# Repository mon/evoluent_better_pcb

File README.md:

# Evoluent VM4/VMC/VMD better PCB

Let's face it - the sensor that Evoluent ships with the VerticalMouse series of
mice is at best "OK" and recently, dreadful. While my VM4 and the wireless VMC
was "fine, but office-spec", the VMD jitters, jumps, and cannot keep up with
even moderately fast moves across the mousepad.

So, I created this drop-in replacement PCB to upgrade the sensor to a gaming
grade PMW3360DM, using an atmega32u4 and Arduino.

## Supported models
So far this seems to work with
- VMD
- VMC
- VM4 (large and small)

It *may* work with the VM3.

The current design only supports wired models.

## Installation

The PCB has the same shape and pinouts as the stock PCB and is a drop-in replacement.

### Step 1
Remove the bottom off your mouse - this unfortunately requires
taking some of the non-slip feet off. Be as careful as possible to not mangle
the feet when you remove them, or you will significantly affect the smooth feel
of the mouse.

**It is normal for surface smoothness to be poor after you replace the feet.
When I upgraded my VMD, it took 2-3 weeks to return to normal feeling.**

For the **Large** VerticalMouse D, the screws (some of which are Torx security
bits) are located here: 

For the VerticalMouse **C**, the screws are located here:  

For the **Small** VerticalMouse 4, the screws are located here:  

### Step 2
With the bottom of the mouse removed, unplug all cables from the existing PCB.

The USB cable (the one located at the back of the PCB) can take a fair amount of
force to remove. Ensure you grip at the base of the cable to avoid damage.

The ribbon cables must also be gripped at the base when removing/replacing them,
as they are more fragile than normal cables.

## Step 3
Unscrew and remove the existing PCB. The screws are located here:

## Step 4
Repeat the disassembly steps in reverse.

## Step 5 (Optional)
For shipped PCBs: If the default firmware is not to your liking, customise it
using the Arduino toolchain. See the "Firmware" section (you can skip the
bootloader as the PCB ships with one).

For PCBs you make yourself: You need to flash the bootloader and firmware, see
the "Firmware" section.

## Firmware

- Using the ICSP pins on the left of the PCB, flash the atmega with the Arduino
  Leonardo bootloader.
- Install the AdvMouse library from the [PMW3360_Arduino
  repository](https://github.com/SunjunKim/PMW3360_Arduino)
- Install the Encoder library under Tools -> Manage Libraries
- The Arduino IDE might not automatically recognise the required files for the project to build. They are:
  - `SROM_0x04_Arduino.ino`
  - `better_evoluent.ino`
  - `usb_rename.cpp`
  - `usb_rename.h`
- Customise your button layout in the struct `button_t buttons[]`.
  - The pin map is:
  - 10: Top mouse button
  - 6: Middle mouse button
  - 4: Lower mouse button
  - 12: Scrollwheel click (for mice that have one)
  - A0: Lower thumb button
  - 2: Upper thumb button
  - (Thumb button pins are reversed on the VMC)
  - 8: Sensitivity/DPI button
- (Optional) Adjust the DPI increments in `dpi_steps[]`
- (Optional) If your buttons are chattery and double-clicking when they
  shouldn't, increase `DEBOUNCE` from 20 to some higher number, such as 50.
- (Optional) Rename the mouse's device name using the `USBRename` line. The
  default is `Evoluent VMD` with manufacturer `mon.im`.
- flash evoluent_better_pcb.ino, selecting Arduino Leonardo as the device type.

I recommend using Device Manager to assign a very high COM port number to the
mouse - that way, you won't accidentally reflash the mouse when working with
other Arduino projects.

The default firmware is basic, but functional. It is based on PMW3360_Arduino's
PMW3360DM-Mouse example and extended for my own uses. It has a serial interface
to configure mouse parameters which is useful when nailing down your preferred
DPI.

The default DPI is the second entry in the list. Clicking the DPI button when
the DPI indicator LEDs are off will show the current DPI. Clicking again within
5 seconds will move the selected DPI through the list. This does not persist
over a power cycle.

## The PCB

It uses the recommended circuit for the PMW3360, with a 1.8v core voltage and
3.3v IO voltage, with the Arduino also running at 3.3v (not 5v).

The PCB is in the `evoluent` subfolder. There are gerbers in `evoluent/production`.

## Assembly/BOM

There is a full BOM csv in `evoluent/production`.

The PMW3360DM (with lens) can be easily bought from aliexpress for about $10
USD.

The FPC connectors for the buttons can be any thru-hole soldered, 1mm pitch
connector. The schematic has the JST 08FMZ-BT/10FMZ-BT, but I ended up buying
something else.

The USB connector is compatible with JST-PH.

The other components are fairly standard, and if the 3v3/1v8 regulators are
unavailable, there will be pin-compatible replacements easily available.

## Support

I use this PCB in my mouse daily. I have been running it for almost 2 years now
without issues, so please get in contact if you are having problems.

You are free to manufacture this PCB and sell it on Tindie etc, just remember to
provide attribution :)

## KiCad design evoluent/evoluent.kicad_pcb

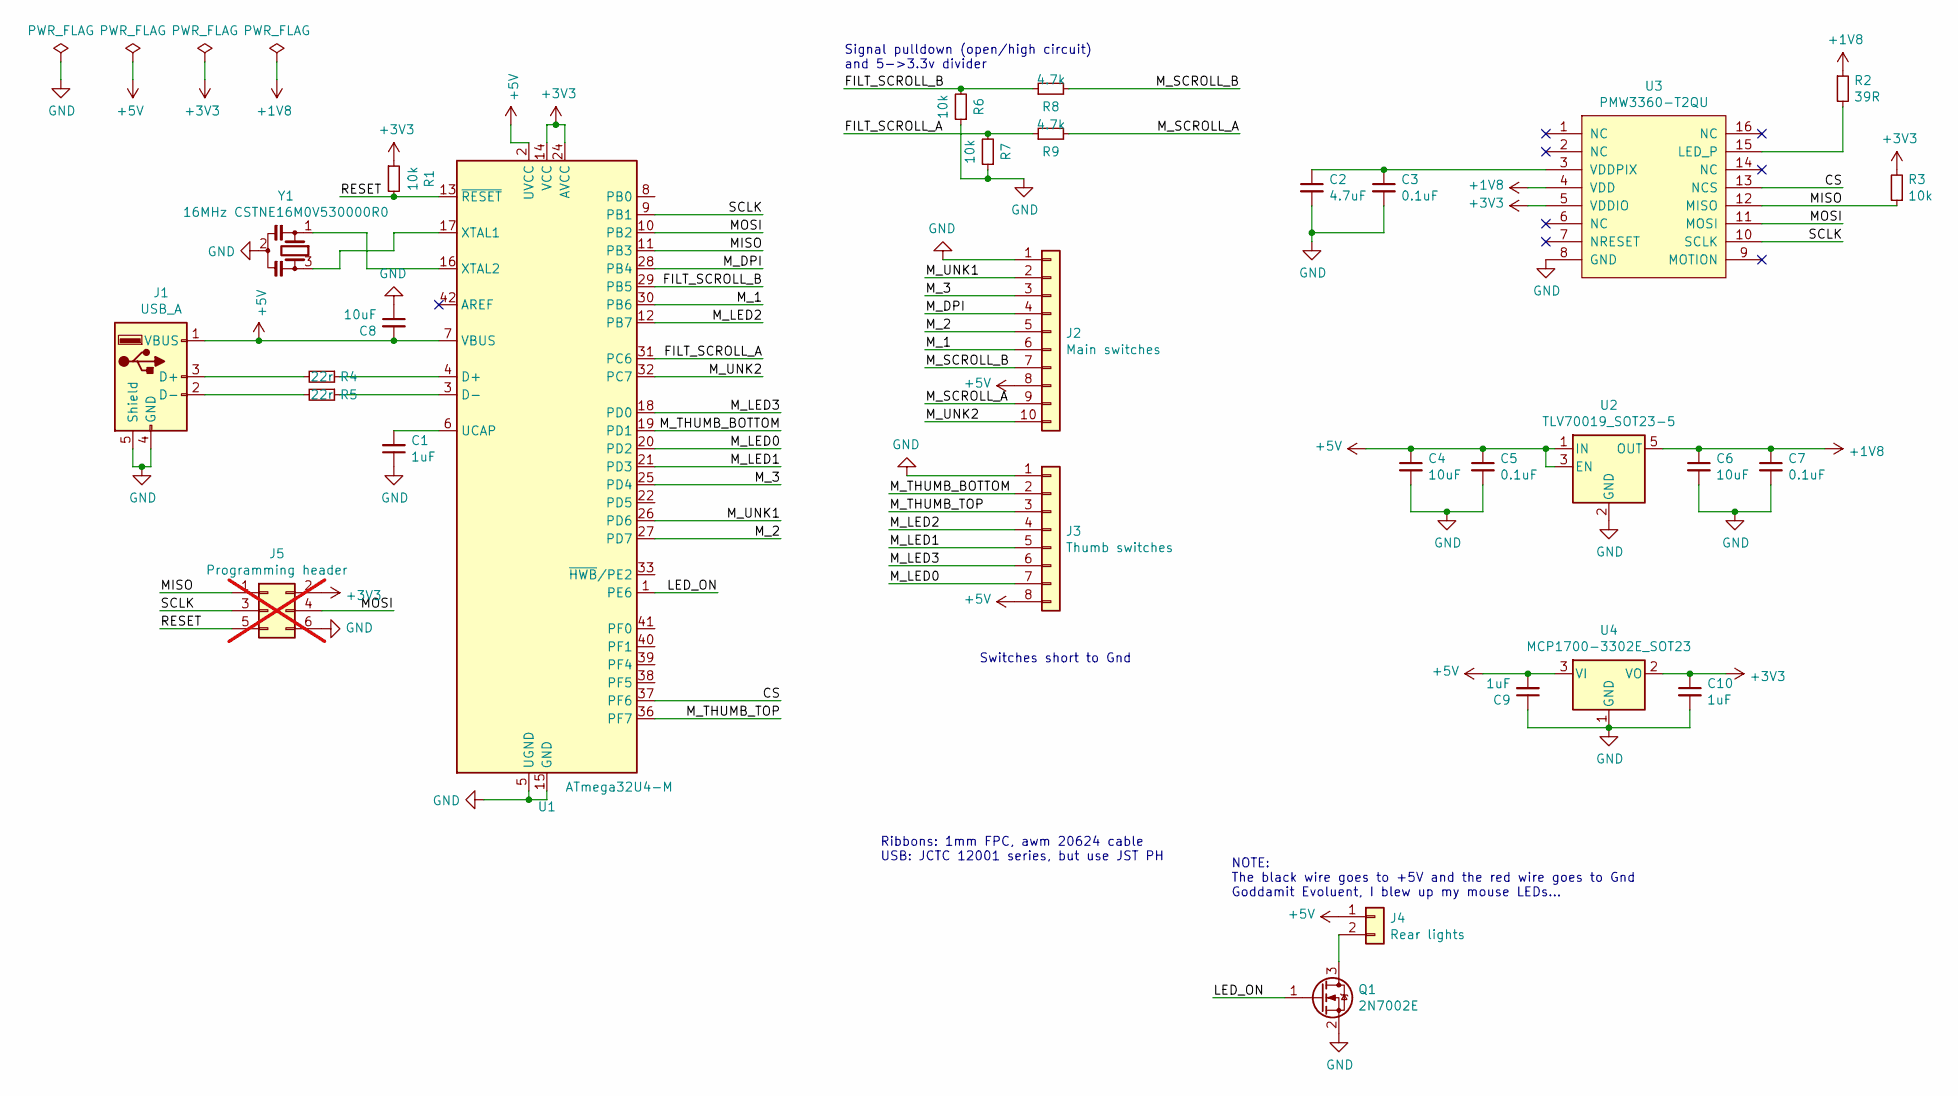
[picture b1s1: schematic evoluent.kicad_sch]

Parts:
C1, C9, C10: 1uF; C_0603_1608Metric; MPN C15849
C2: 4.7uF; C_0603_1608Metric; MPN C19666
C3, C5, C7: 0.1uF; C_0603_1608Metric; MPN C14663
C4, C6, C8: 10uF; C_0603_1608Metric; MPN C19702
J1: USB_A; JST_PH_B5B-PH-K_1x05_P2.00mm_Vertical; MPN C157993
J2: Main switches; 10FMZ-BT; MPN C2908574
J3: Thumb switches; 08FMZ-BT; MPN C94606
J4: Rear lights; Molex_PicoBlade_53047-0210_1x02_P1.25mm_Vertical; MPN C114130
J5: Programming header; PinHeader_2x03_P2.54mm_Vertical; not fitted
Q1: 2N7002E; SOT-23; MPN C350312
R1, R3, R6, R7: 10k; R_0603_1608Metric; MPN C25804
R2: 39R; R_0603_1608Metric; MPN C23038
R4, R5: 22r; R_0603_1608Metric; MPN C23345
R8, R9: 4.7k; R_0603_1608Metric; MPN C23162
U1: ATmega32U4-M; QFN-44-1EP_7x7mm_P0.5mm_EP5.2x5.2mm; MPN C112161
U2: TLV70019_SOT23-5; SOT-23-5; MPN C697975
U3: PMW3360-T2QU
U4: MCP1700-3302E_SOT23; SOT-23; MPN C5148692
Y1: 16MHz CSTNE16M0V530000R0; Resonator_SMD_muRata_CSTxExxV-3Pin_3.0x1.1mm; MPN C341521

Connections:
+1V8: C6.1, C7.1, R2.1, U2.5 (OUT), U3.4 (VDD)
+3V3: C10.1, J5.2, R1.1, R3.2, U1.14 (VCC), U1.24 (AVCC), U1.34 (VCC), U1.44 (AVCC), U3.5 (VDDIO), U4.2 (VO)
+5V: C4.1, C5.1, C8.2, C9.2, J1.1 (VBUS), J2.8, J3.8, J4.1, U1.2 (UVCC), U1.7 (VBUS), U2.1 (IN), U2.3 (EN), U4.3 (VI)
/CS: U1.37 (PF6), U3.13 (NCS)
/FILT_SCROLL_A: R7.2, R9.1, U1.31 (PC6)
/FILT_SCROLL_B: R6.2, R8.1, U1.29 (PB5)
/LED_ON: Q1.1 (G), U1.1 (PE6)
/MISO: J5.1, R3.1, U1.11 (PB3), U3.12 (MISO)
/MOSI: J5.4, U1.10 (PB2), U3.11 (MOSI)
/M_1: J2.6, U1.30 (PB6)
/M_2: J2.5, U1.27 (PD7)
/M_3: J2.3, U1.25 (PD4)
/M_DPI: J2.4, U1.28 (PB4)
/M_LED0: J3.7, U1.20 (PD2)
/M_LED1: J3.5, U1.21 (PD3)
/M_LED2: J3.4, U1.12 (PB7)
/M_LED3: J3.6, U1.18 (PD0)
/M_SCROLL_A: J2.9, R9.2
/M_SCROLL_B: J2.7, R8.2
/M_THUMB_BOTTOM: J3.2, U1.19 (PD1)
/M_THUMB_TOP: J3.3, U1.36 (PF7)
/M_UNK1: J2.2, U1.26 (PD6)
/M_UNK2: J2.10, U1.32 (PC7)
/RESET: J5.5, R1.2, U1.13 (~RESET)
/SCLK: J5.3, U1.9 (PB1), U3.10 (SCLK)
GND: C1.1, C2.2, C3.2, C4.2, C5.2, C6.2, C7.2, C8.1, C9.1, C10.2, J1.4 (GND), J1.5 (Shield), J2.1, J3.1, J5.6, Q1.2 (S), R6.1, R7.1, U1.5 (UGND), U1.15 (GND), U1.23 (GND), U1.35 (GND), U1.43 (GND), U1.45 (GND), U2.2 (GND), U3.8 (GND), U4.1 (GND), Y1.2
unnamed: J1.3 (D+), R4.2
unnamed: J1.2 (D-), R5.2
unnamed: J4.2, Q1.3 (D)
unnamed: R4.1, U1.4 (D+)
unnamed: R5.1, U1.3 (D-)
unnamed: C1.2, U1.6 (UCAP)
unnamed: U1.17 (XTAL1), Y1.3
unnamed: U1.16 (XTAL2), Y1.1
unnamed: R2.2, U3.15 (LED_P)
unnamed: C2.1, C3.1, U3.3 (VDDPIX)

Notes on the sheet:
Ribbons: 1mm FPC, awm 20624 cable USB: JCTC 12001 series, but use JST PH
Signal pulldown (open/high circuit) and 5->3.3v divider
NOTE: The black wire goes to +5V and the red wire goes to Gnd Goddamit Evoluent, I blew up my mouse LEDs...
Switches short to Gnd

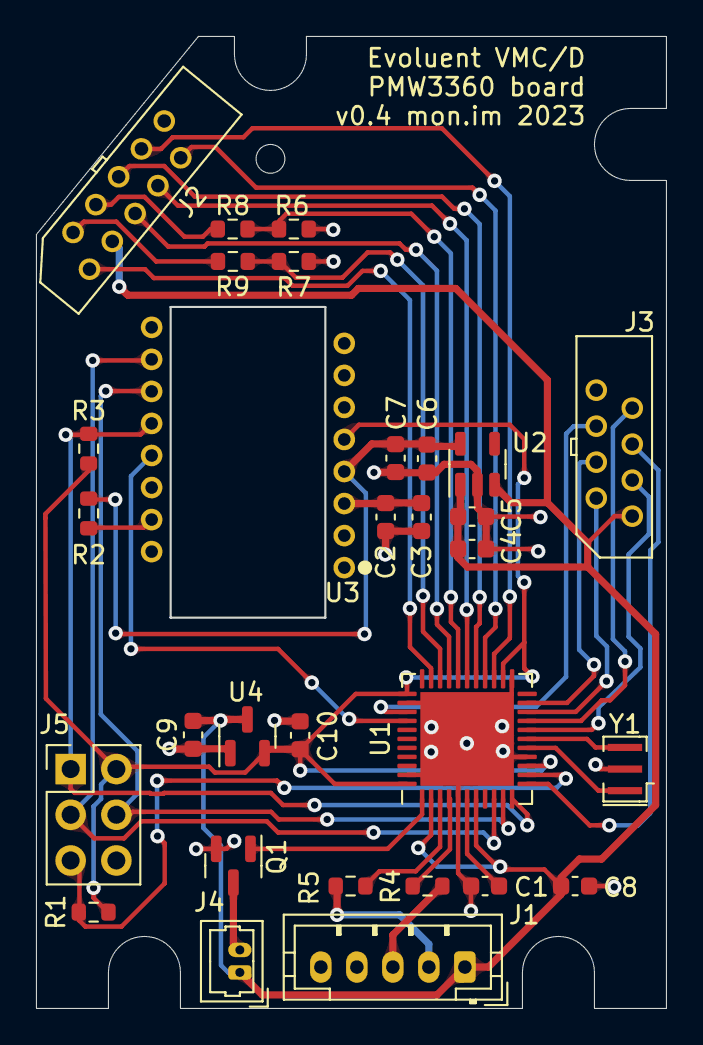
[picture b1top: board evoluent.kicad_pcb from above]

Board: 2 copper layers, 34.9 x 53.9 mm, 30 parts (0 on the bottom side), 36 nets.

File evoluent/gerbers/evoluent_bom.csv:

"Source:","evoluent_better_pcb\evoluent\evoluent.sch"
"Date:","4/01/2021 8:30:48 PM"
"Tool:","Eeschema (5.1.5)-3"
"Generator:","C:\Program Files\KiCad\bin\scripting\plugins/bom_csv_grouped_by_value_with_fp.py"
"Component Count:","30"
"Ref","Qnty","Value","Cmp name","Footprint","Description","Vendor"
"C1, C9, C10, ","3","1uF","C_Small","Capacitor_SMD:C_0603_1608Metric","Unpolarized capacitor, small symbol",""
"C2, ","1","4.7uF","C_Small","Capacitor_SMD:C_0603_1608Metric","Unpolarized capacitor, small symbol",""
"C3, C5, C7, ","3","0.1uF","C_Small","Capacitor_SMD:C_0603_1608Metric","Unpolarized capacitor, small symbol",""
"C4, C6, C8, ","3","10uF","C_Small","Capacitor_SMD:C_0603_1608Metric","Unpolarized capacitor, small symbol",""
"J1, ","1","USB_A","USB_A","Connector_JST:JST_PH_B5B-PH-K_1x05_P2.00mm_Vertical","USB Type A connector",""
"J2, ","1","Main switches","Conn_01x10","Evoluent:10FMZ-BT","Generic connector, single row, 01x10, script generated (kicad-library-utils/schlib/autogen/connector/)",""
"J3, ","1","Thumb switches","Conn_01x08","Evoluent:08FMZ-BT","Generic connector, single row, 01x08, script generated (kicad-library-utils/schlib/autogen/connector/)",""
"J4, ","1","Rear lights","Conn_01x02","Connector_Molex:Molex_PicoBlade_53047-0210_1x02_P1.25mm_Vertical","Generic connector, single row, 01x02, script generated (kicad-library-utils/schlib/autogen/connector/)",""
"J5, ","1","Programming header","Conn_02x03_Odd_Even","Connector_PinHeader_2.54mm:PinHeader_2x03_P2.54mm_Vertical","Generic connector, double row, 02x03, odd/even pin numbering scheme (row 1 odd numbers, row 2 even numbers), script generated (kicad-library-utils/schlib/autogen/connector/)",""
"Q1, ","1","2N7002E","2N7002E","Package_TO_SOT_SMD:SOT-23","0.24A Id, 60V Vds, N-Channel MOSFET, SOT-23",""
"R1, R3, R6, R7, ","4","10k","R_Small","Resistor_SMD:R_0603_1608Metric","Resistor, small symbol",""
"R2, ","1","39R","R_Small","Resistor_SMD:R_0603_1608Metric","Resistor, small symbol",""
"R4, R5, ","2","22r","R_Small","Resistor_SMD:R_0603_1608Metric","Resistor, small symbol",""
"R8, R9, ","2","4.7k","R_Small","Resistor_SMD:R_0603_1608Metric","Resistor, small symbol",""
"U1, ","1","ATmega32U4-AU","ATmega32U4-AU","Package_QFP:TQFP-44_10x10mm_P0.8mm","16MHz, 32kB Flash, 2.5kB SRAM, 1kB EEPROM, USB 2.0, TQFP-44",""
"U2, ","1","TLV70019_SOT23-5","TLV70019_SOT23-5","Package_TO_SOT_SMD:SOT-23-5","200mA Low Dropout Voltage Regulator, Fixed Output 1.9V, SOT-23-5",""
"U3, ","1","PMW3360-T2QU","PMW3360-T2QU","Evoluent:PMW3360-T2QU","",""
"U4, ","1","MCP1700-3302E_SOT23","MCP1700-3302E_SOT23","Package_TO_SOT_SMD:SOT-23","250mA Low Quiscent Current LDO, 3.3V output, SOT-23",""
"Y1, ","1","8MHz CSTNE8M00G550000R0","Resonator_Small","Evoluent:Resonator_SMD_muRata_CSTxExxV-3Pin_3.0x1.1mm","Three pin ceramic resonator, small symbol",""

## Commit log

2023-09-23 v0.4
2023-09-24 Note about security bits
